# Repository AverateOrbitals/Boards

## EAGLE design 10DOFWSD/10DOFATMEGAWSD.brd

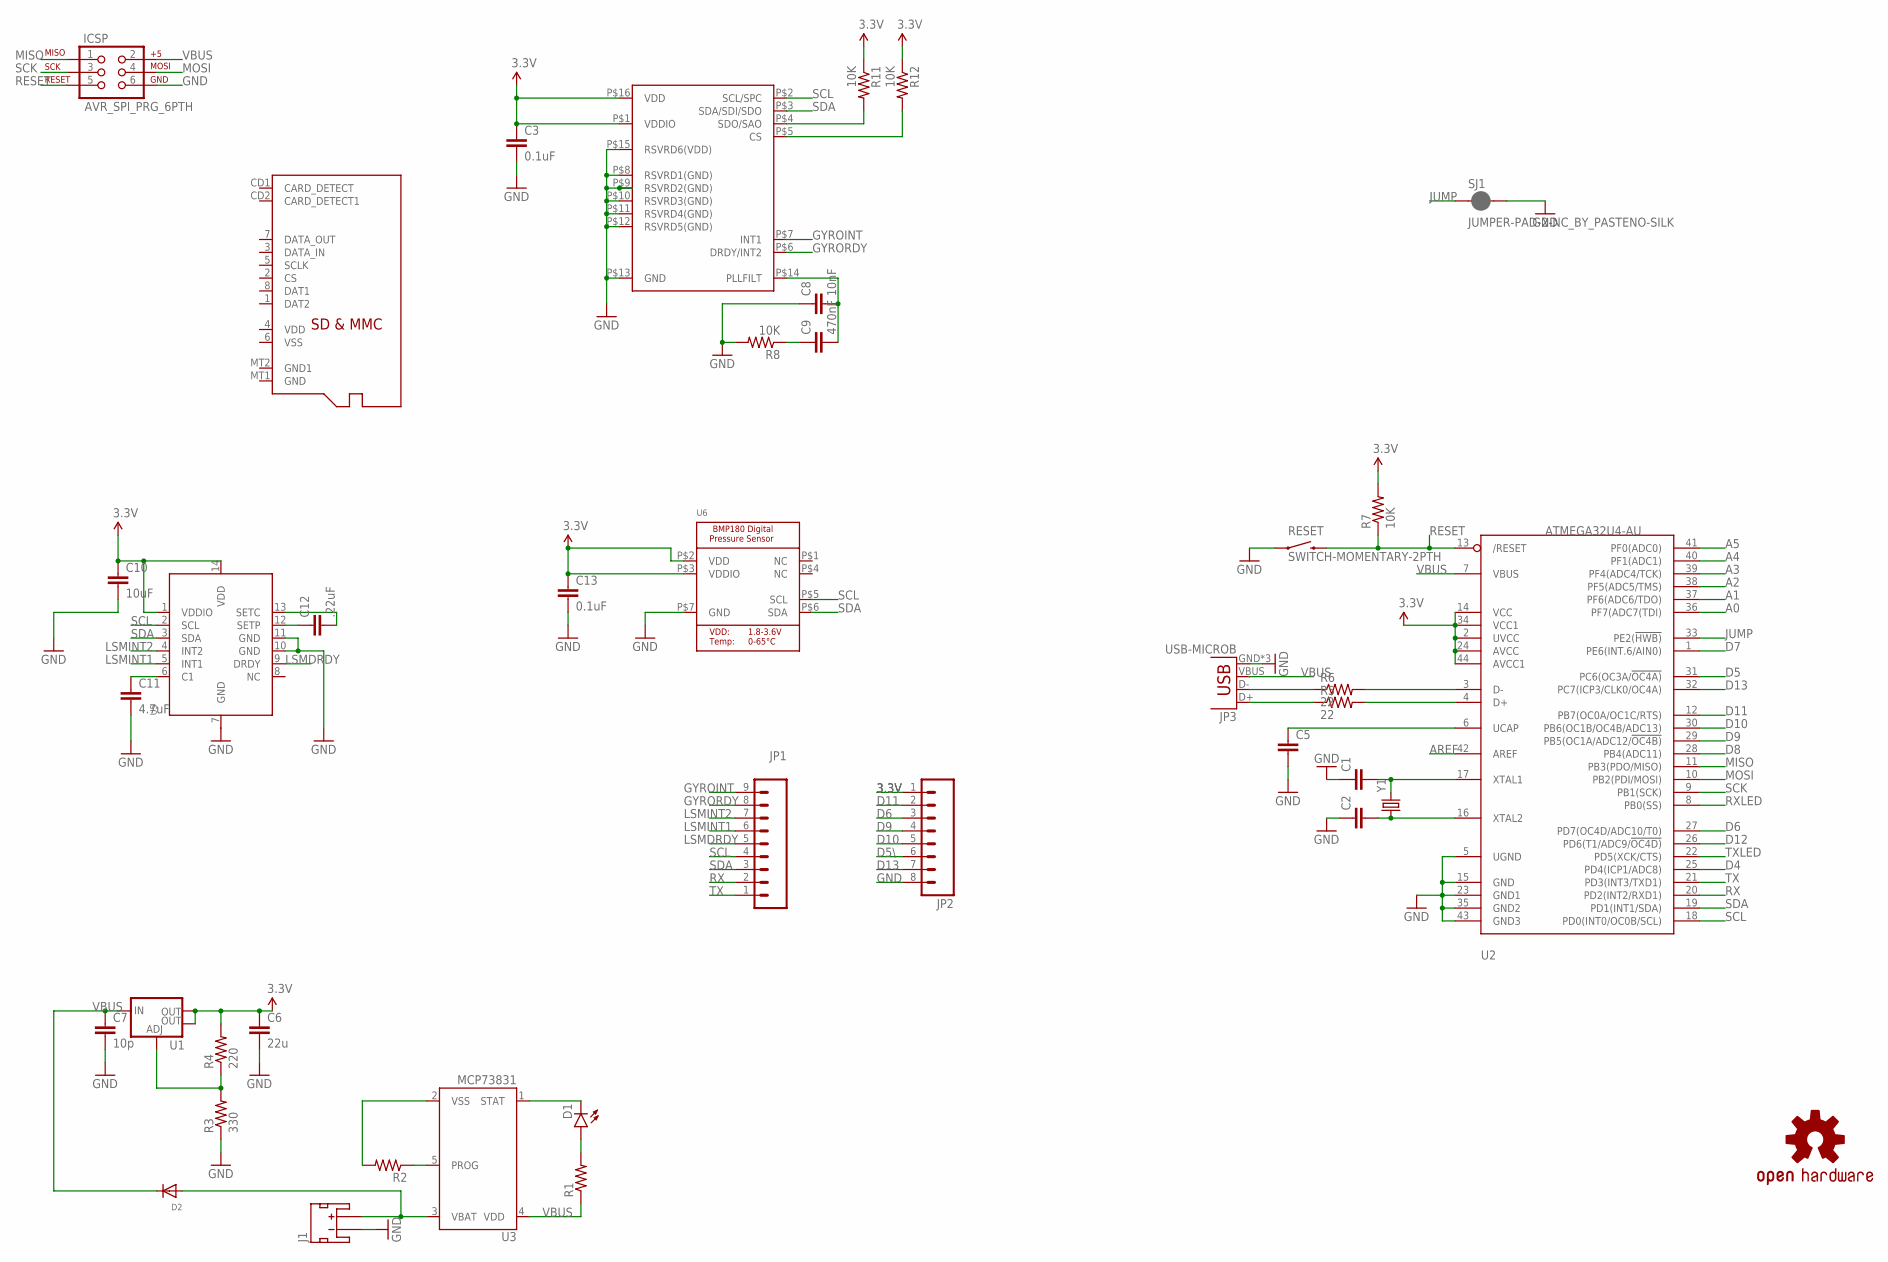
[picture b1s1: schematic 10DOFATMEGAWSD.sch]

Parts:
C1, C2, C5: CAP0603-CAP; 0603-CAP
C3, C13: 0.1uF; 0603-CAP
C6: 22u; 0603-CAP
C7: 10p; 0603-CAP
C8: 10nF; 0603-CAP
C9: 470nF; 0603-CAP
C10: 10uF; 0603-CAP
C11: 4.7uF; 0603-CAP
C12: .22uF; 0603-CAP
D1: LED3MM
D2: DIODESOT23_REFLOW; SOT23-R
ICSP: AVR_SPI_PRG_6PTH; 2X3
J1: JST_2MM_MALE; JST-2-SMD
JP1: M09; 1X09
JP2: M08; 1X08_ROUND
JP3: USB-MICROB
LOGO1: OSHW-LOGOS-COPPER; OSHW-LOGO-S_COPPER
R1, R2: RESISTOR0603-RES; 0603-RES
R3: 330; 0603-RES
R4: 220; 0603-RES
R5, R6: 22; 0603-RES
R7, R8, R11, R12: 10K; 0603-RES
RESET: SWITCH-MOMENTARY-2PTH; TACTILE-PTH
SJ1: JUMPER-PAD-2-NC_BY_PASTENO-SILK; PAD-JUMPER-2-NC_BY_PASTE_NO_SILK
U1: V_REG_LM1117SOT223; SOT223
U2: ATMEGA32U4-AU; TQFP44
U3: MCP73831; SOT23-5
U4: GYRO_L3G2400D; L3G4200D_LGA16L
U5: LSM303DLHC; LGA14
U6: BMP180EXT; BMP180_EXTENDED
U$1: MICROSD
Y1: CRYSTALHC49US; HC49US

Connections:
3.3V: C3.1, C6.1, C10.1, C13.1, JP2.1, R4.2, R7.2, R11.1, R12.1, U1.2 (OUT), U1.4 (OUT), U2.2 (UVCC), U2.14 (VCC), U2.24 (AVCC), U2.34 (VCC1), U2.44 (AVCC1), U4.P$1 (VDDIO), U4.P$16 (VDD), U5.1 (VDDIO), U5.14 (VDD), U6.P$2 (VDD), U6.P$3 (VDDIO)
A0: U2.36 (PF7(ADC7(TDI))
A1: U2.37 (PF6(ADC6/TDO))
A2: U2.38 (PF5(ADC5/TMS))
A3: U2.39 (PF4(ADC4/TCK))
A4: U2.40 (PF1(ADC1))
A5: U2.41 (PF0(ADC0))
AREF: U2.42 (AREF)
D4: U2.25 (PD4(ICP1/ADC8))
D5: U2.31 (PC6(OC3A/!OC4A))
D5\: JP2.6
D6: JP2.3, U2.27 (PD7(OC4D/ADC10/T0))
D7: U2.1 (PE6(INT.6/AIN0))
D8: U2.28 (PB4(ADC11))
D9: JP2.4, U2.29 (PB5(OC1A/ADC12/!OC4B))
D10: JP2.5, U2.30 (PB6(OC1B/OC4B/ADC13))
D11: JP2.2, U2.12 (PB7(OC0A/OC1C/RTS))
D12: U2.26 (PD6(T1/ADC9/!OC4D))
D13: JP2.7, U2.32 (PC7(ICP3/CLK0/OC4A))
GND: C1.1, C2.1, C3.2, C5.2, C6.2, C7.2, C8.1, C10.2, C11.2, C13.2, ICSP.6, J1.1 (-), JP2.8, JP3.GND, JP3.MT1 (GND), JP3.MT2 (GND), R3.1, R8.2, RESET.1, SJ1.2, U2.5 (UGND), U2.15 (GND), U2.23 (GND1), U2.35 (GND2), U2.43 (GND3), U4.P$8 (RSVRD1(GND)), U4.P$9 (RSVRD2(GND)), U4.P$10 (RSVRD3(GND)), U4.P$11 (RSVRD4(GND)), U4.P$12 (RSVRD5(GND)), U4.P$13 (GND), U4.P$15 (RSVRD6(VDD)), U5.7 (GND), U5.10 (GND), U5.11 (GND), U6.P$7 (GND)
GYROINT: JP1.9, U4.P$7 (INT1)
GYRORDY: JP1.8, U4.P$6 (DRDY/INT2)
JUMP: SJ1.1, U2.33 (PE2(!HWB))
LSMDRDY: JP1.5, U5.9 (DRDY)
LSMINT1: JP1.6, U5.5 (INT1)
LSMINT2: JP1.7, U5.4 (INT2)
MISO: ICSP.1, U2.11 (PB3(PDO/MISO))
MOSI: ICSP.4, U2.10 (PB2(PDI/MOSI))
unnamed: C2.2, U2.16 (XTAL2), Y1.1
unnamed: C1.2, U2.17 (XTAL1), Y1.2
unnamed: R5.2, U2.4 (D+)
unnamed: R6.2, U2.3 (D-)
unnamed: R2.1, U3.5 (PROG)
unnamed: R2.2, U3.2 (VSS)
unnamed: D1.K (C), U3.1 (STAT)
unnamed: D1.A, R1.2
unnamed: JP3.D+, R5.1
unnamed: R3.2, R4.1, U1.1 (ADJ)
unnamed: JP3.D-, R6.1
unnamed: R11.2, U4.P$4 (SDO/SAO)
unnamed: D2.1 (A), J1.2 (+), U3.3 (VBAT)
unnamed: R12.2, U4.P$5 (CS)
unnamed: C8.2, C9.2, U4.P$14 (PLLFILT)
unnamed: C9.1, R8.1
unnamed: C11.1, U5.6 (C1)
unnamed: C12.2, U5.13 (SETC)
unnamed: C12.1, U5.12 (SETP)
unnamed: C5.1, U2.6 (UCAP)
RESET: ICSP.5, R7.1, RESET.3 (2), U2.13 (/RESET)
RX: JP1.2, U2.20 (PD2(INT2/RXD1))
RXLED: U2.8 (PB0(SS))
SCK: ICSP.3, U2.9 (PB1(SCK))
SCL: JP1.4, U2.18 (PD0(INT0/OC0B/SCL)), U4.P$2 (SCL/SPC), U5.2 (SCL), U6.P$5 (SCL)
SDA: JP1.3, U2.19 (PD1(INT1/SDA)), U4.P$3 (SDA/SDI/SDO), U5.3 (SDA), U6.P$6 (SDA)
TX: JP1.1, U2.21 (PD3(INT3/TXD1))
TXLED: U2.22 (PD5(XCK/CTS))
VBUS: C7.1, D2.3 (C), ICSP.2, JP3.VBUS, R1.1, U1.3 (IN), U2.7 (VBUS), U3.4 (VDD)

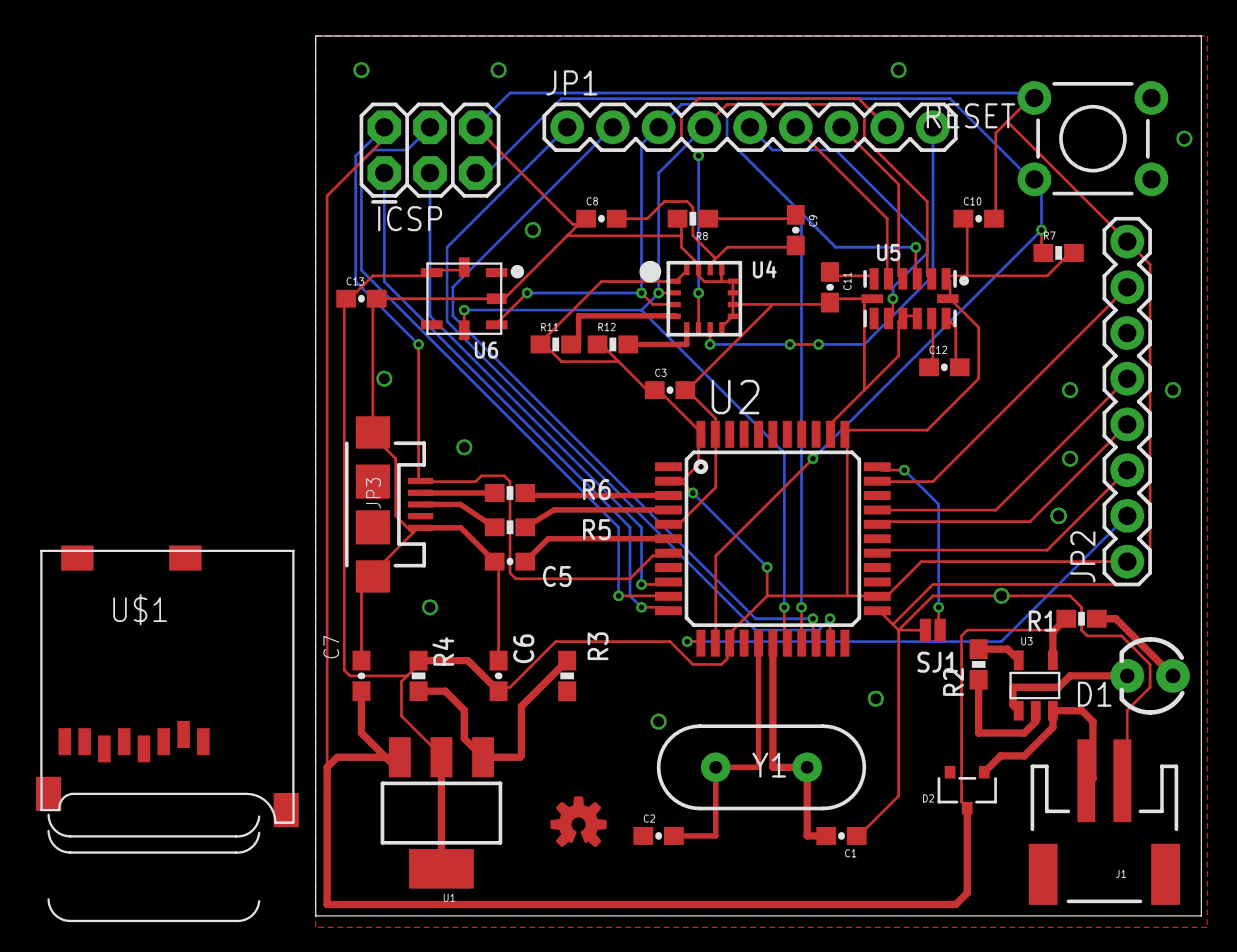
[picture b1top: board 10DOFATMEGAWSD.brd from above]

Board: 2 copper layers, 49.2 x 48.9 mm, 40 parts (0 on the bottom side), 42 nets.

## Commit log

2015-12-27 Adding Boards
    Boards Added

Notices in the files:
parts and their libraries:
SparkFun-Capacitors: Licensing: Creative Commons ShareAlike 4.0 International - https://creativecommons.org/licenses/by-sa/4.0
microbuilderLib: This work is placed in the public domain, and may be freely used for commercial and non-commercial work with the following conditions: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
